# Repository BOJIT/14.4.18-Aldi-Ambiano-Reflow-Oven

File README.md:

# Aldi Ambiano Reflow Oven
Dirt cheap, easily replicable SMD reflow oven based on an Arduino Nano
and the £19.99 Aldi Ambiano Mini Oven

Developers: James Bennion-Pedley

Firmware closely based on work by https://github.com/giacu92/Arduino-Reflow-Oven-Controller

Project Write-Up Here: [https://bojit.dev/projects/Reflow_Oven/]

BOJIT Development Team

GPLv3 License

Copyright (c) 2018 BOJIT

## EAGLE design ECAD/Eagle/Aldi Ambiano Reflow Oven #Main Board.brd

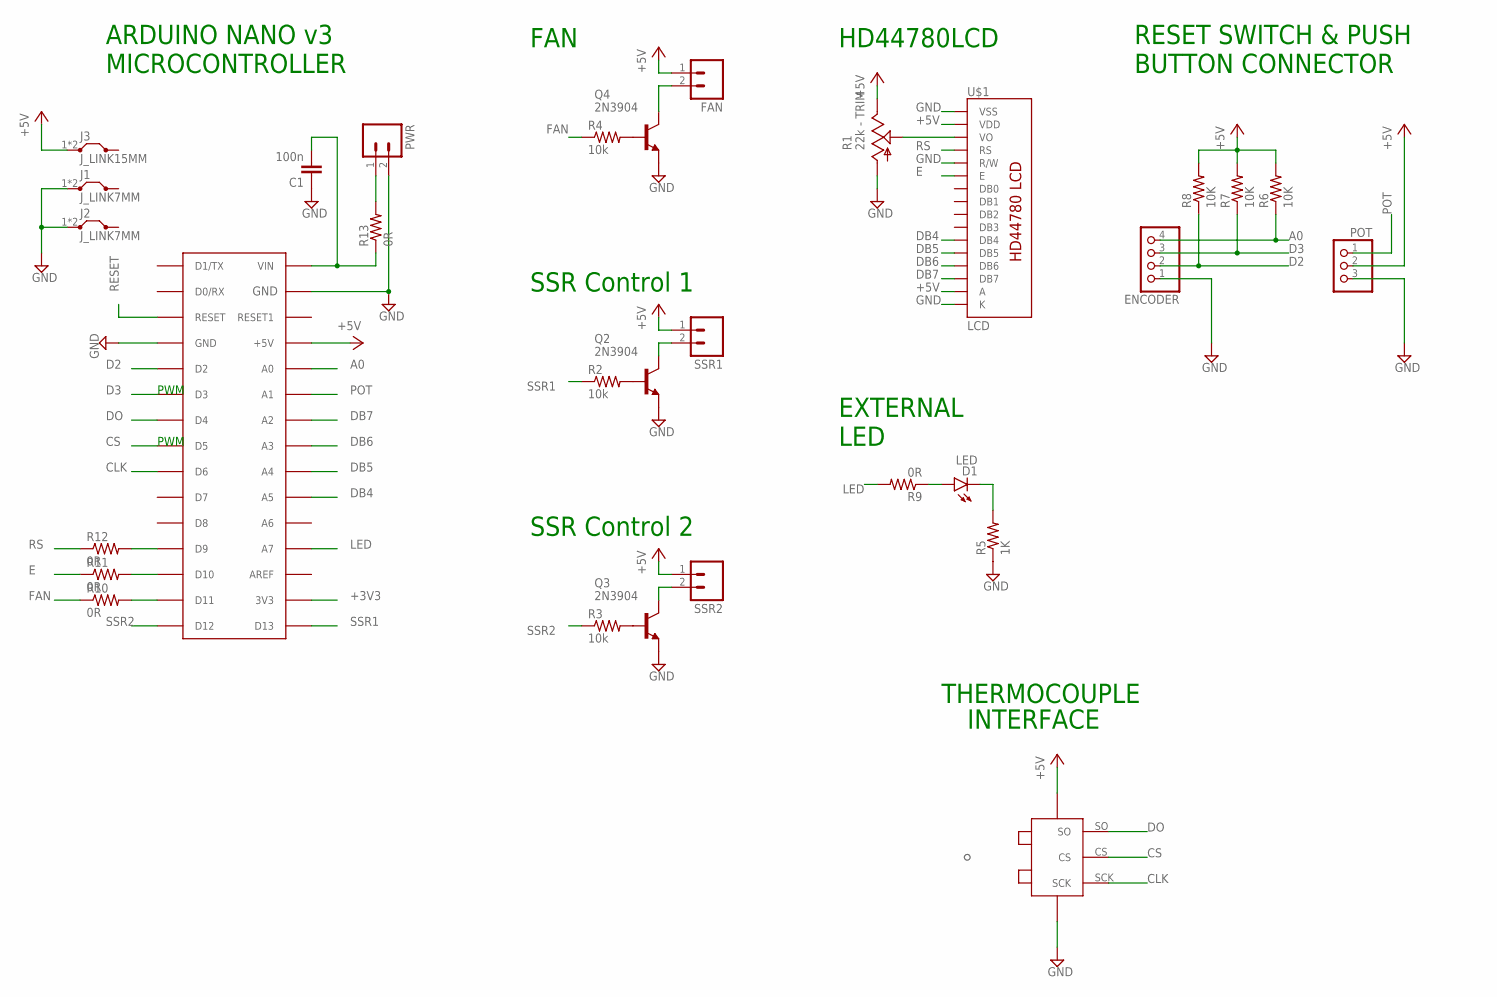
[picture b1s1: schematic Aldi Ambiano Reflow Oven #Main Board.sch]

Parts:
ARDUINO: Arduino Nano v3.0; PDIP-32
C1: 100n; CAP-PTH-5MM
D1: LED; LED3MM
ENCODER: PINHD-1X4/90; 1X04/90
FAN: M025MM; SCREWTERMINAL-5MM-2
J1, J2: J_LINK7MM; 07
J3: J_LINK15MM; 15
POT: PINHD-1X3/90; 1X03/90
PWR: M025MM; SCREWTERMINAL-5MM-2
Q2, Q3, Q4: 2N3904; TO92
R1: 22k - TRIM; CA9V
R2, R3, R4: 10k; R0207/3
R5: 1K; R0207/3
R6, R8: 10K; R0207/4
R7: 10K; R0207/3
R9: 0R; R0207/4
R10, R12: 0R; R0207/3
R11: 0R; R0207/6
R13: 0R; R0207/5
SSR1, SSR2: M025MM; SCREWTERMINAL-5MM-2
U$1: LCD; LCD-16X2-4HOLES
U$2: MAX6675_BREAKOUT

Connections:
+3V3: ARDUINO.3V3
+5V: ARDUINO.+5V, FAN.1, J3.1, J3.2, POT.2, R1.E, R6.2, R7.2, R8.2, SSR1.1, SSR2.1, U$1.2 (VDD), U$1.15 (A), U$2.VCC
A0: ARDUINO.A0, ENCODER.4, R6.1
CLK: ARDUINO.D6, U$2.SCK
CS: ARDUINO.D5, U$2.CS
D2: ARDUINO.D2, ENCODER.2, R8.1
D3: ARDUINO.D3, ENCODER.3, R7.1
DB4: ARDUINO.A5, U$1.11 (DB4)
DB5: ARDUINO.A4, U$1.12 (DB5)
DB6: ARDUINO.A3, U$1.13 (DB6)
DB7: ARDUINO.A2, U$1.14 (DB7)
DO: ARDUINO.D4, U$2.SO
E: R11.1, U$1.6 (E)
EINT: ARDUINO.D10, R11.2
FAN: R4.1, R10.1
FANJOINT: ARDUINO.D11, R10.2
GND: ARDUINO.GND, ARDUINO.GND1 (GND), C1.1, ENCODER.1, J1.1, J1.2, J2.1, J2.2, POT.3, PWR.2, Q2.3 (E), Q3.3 (E), Q4.3 (E), R1.A, R5.1, U$1.1 (VSS), U$1.5 (R/W), U$1.16 (K), U$2.GND
LED: ARDUINO.A7, R9.2
LEDINT: D1.A, R9.1
unnamed: PWR.1, R13.2
unnamed: Q2.1 (C), SSR1.2
unnamed: Q2.2 (B), R2.2
unnamed: R1.S, U$1.3 (VO)
unnamed: D1.K (C), R5.2
unnamed: Q3.1 (C), SSR2.2
unnamed: Q3.2 (B), R3.2
unnamed: FAN.2, Q4.1 (C)
unnamed: Q4.2 (B), R4.2
POT: ARDUINO.A1, POT.1
RESET: ARDUINO.RESET
RS: R12.1, U$1.4 (RS)
RSINT: ARDUINO.D9, R12.2
SSR1: ARDUINO.D13, R2.1
SSR2: ARDUINO.D12, R3.1
VIN: ARDUINO.VIN, C1.2, R13.1

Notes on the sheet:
SSR Control 1
THERMOCOUPLE
INTERFACE
ARDUINO NANO v3 MICROCONTROLLER
HD44780LCD
EXTERNAL LED
RESET SWITCH & PUSH BUTTON CONNECTOR
PWM
SSR Control 2
FAN

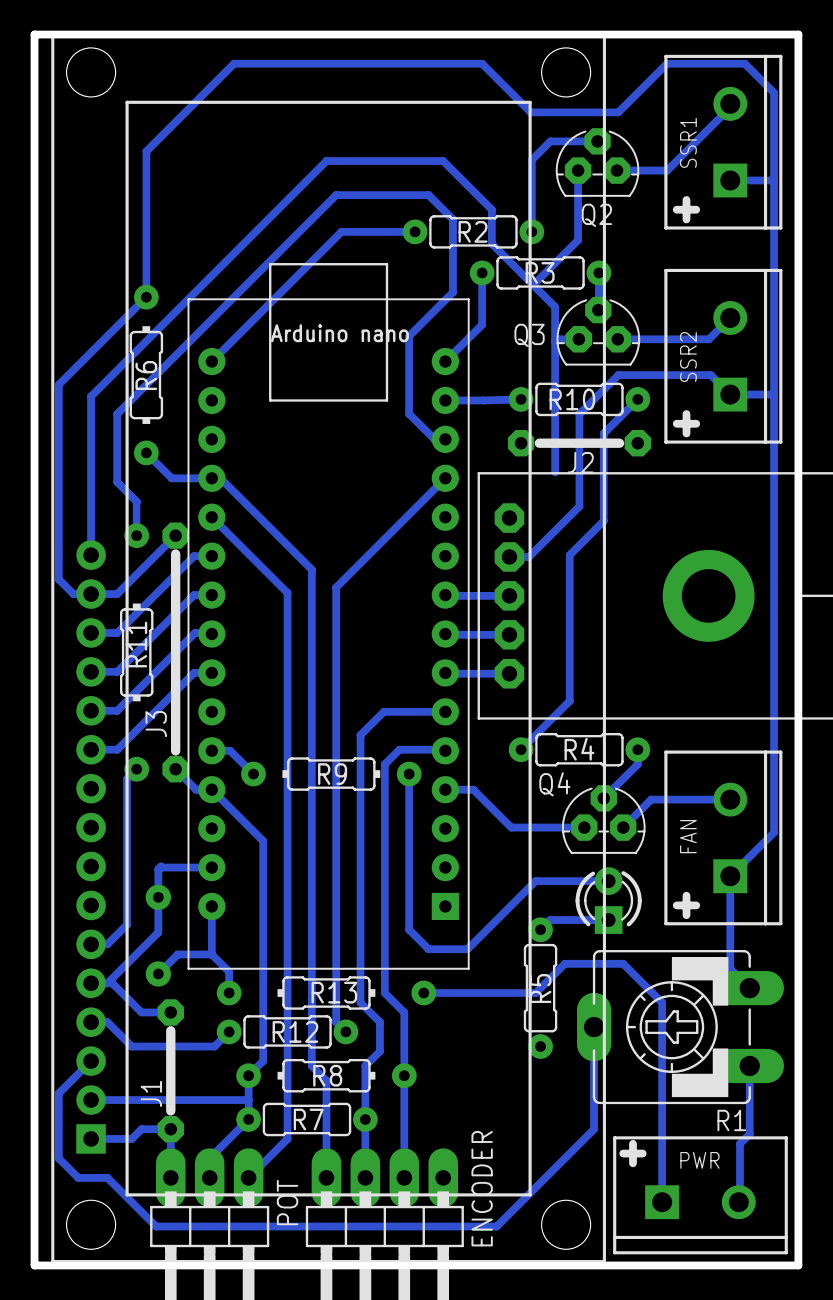
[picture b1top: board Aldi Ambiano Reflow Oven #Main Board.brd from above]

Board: 2 copper layers, 49.8 x 80.3 mm, 30 parts (1 on the bottom side), 33 nets.

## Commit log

2018-04-15 Pad Clearance Changed
2019-06-23 folder structure + attribution
2019-06-23 Create LICENSE
2019-06-23 addd BOM

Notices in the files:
parts and their libraries:
SparkFun-Connectors: Licensing: Creative Commons ShareAlike 4.0 International - https://creativecommons.org/licenses/by-sa/4.0
